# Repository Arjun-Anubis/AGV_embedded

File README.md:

# AGV Embedded Systems Selection Round

I attempted the first two tasks, the PCB design of the nPM1100 and the digital design of CORDIC in verilog

## Structure of the Repository

The task folders each have their directories, within the first level, the README.md
will have the info required to run the programs including installation directions etc
The documentation and approach will be in the doc folder

## Progress on the tasks

### PCB design

1. Base task (design req)
    a. Schematic
    b. Design 
    c. BOM
2. Expose CHG, ERR, ISET, MODE, SHPHLD and SHPACT pins to MCU
3. Status LEDs
4. Battery Monitoring

Constraints
1. Max Dimensions
2. SMD, top mounted
3. 0403-0805 footprints
4. Input via 2 pin header       NOTE
5. Max 4 copper layers
6. QFN24 footprint with used central thermal pad
7. 3V output
8. 200mA output

### Digital Design

1. Design
    a. n-bit adder
    b. complemts and subtracter
    c. comparator
    d. look up table
    e. 8 bit to 12 bit CORDIC
2. Test Bench
3. GTKWave

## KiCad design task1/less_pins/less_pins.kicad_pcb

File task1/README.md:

# PCB Design with the nPM1100 PMIC

This is documentaion written after the fact, if you want to read the 
design process as it was done, consider [the old readme](./README.old.md). 
I'll explain my model in two layers of abstraction.

1. Behaviour level
2. Pin level

## Behaviour level

A PMIC is typically used on a portable electronic device: like a mobile phone, 
a gaming mouse, a drone etc. it abstracts away the details of charging and battery
and provides a stable voltage and current to the microcontroller chip.

This means that our chip has the following

1. input (USB or barrel)
2. output (microcontroller)
3. inout (battery, which has to be charged and discharged)

and similarly out PMIC can itself be divided into subsystems

Now that we understand what the chip does on a high level, we need to check if this
is indeed the right chip for us to use, we can decide this by looking at the 
design requirements:

1. 3V DC output
2. 200mA charging
3. 35mmx35mm for the entire PCB

and we have been told to use the nordic semiconductor nPM1100 PMIC
with the QFN24 variant, which is 4mmx4mm.

First we make a ballpark estimate, then we consult the data sheet, the voltage ~ 3V
is pretty typical for a microcontroller so that makes sense, and the charging
current 200mA is pretty typical for a small LiPo battery, in say a drone.

The consumption current is probably less than that, and that would make the 
outut power a few hundred mW, which is also reasonable for a 35mmx35mm
chip to discharge

Now we consult the datasheet

### Package size

The 4mmx4mm package does indeed exist

> nPM1100 is an integrated Power Management IC (PMIC) with a linear-mode lithium-ion/lithium-polymer battery charger in a compact 2.1x2.1 mm WLCSP or 4.0x4.0 mm QFN package. It has a highly efficient DC/ DC buck regulator with configurable dual mode output.

and we can indeed order it, according to the datasheet, the exact variant we want is

> nPM1100-QDAA-XX

where the QD portion signifies the QFN package, and AA specifies the Vterm voltage

### Charging Current

We can indeed charge at 200mA 

> Configurable charge current with a resistor connected to the ICHG pin (from 20 mA to 400 mA)

and we need to use a 1.5k resistor according to the table

### Output voltage

We can indeed output a stable 3.0V using the buck regulator

> Configurable output voltage between 1.8 V and 3.0 

and we need to set both VOUTBSET pins high accourding to the table

## Pin Level

Now we have a high level overview of the scale and function of the chip, and we haev determined
that it can be appropriately used here, let us get into the nitty gritties. We need to make a few 
design choices

1. Which power input setting?

According to the datasheet, I can choose from four possible choices, of these I'm going to choose 
option 3, 

Why? Three reasons

a. We need atleast 200mA input for it to be able to charge the battery while also powering the device
and so I cant use the flat 100mA option
b. Flat 500mA is unsafe in the SDP case, in which case I risk bricking a laptop if I charge from that
essentially I wouldnt be following the USB spec
c. Exposing ISET requires (a) more pins to the MCU, and (b) also exposing the usb data line to the MCU
both of which, it may not have

2. Which battery parameters?
We need to set three parameters;

a. Ichg, which has to be 200mA and requires a 1.5k resistor (tolerance be damned :( )
b. Vtermset, which really depends on our battery, but I'll set it low, which is 4.1V cuz we're on standard
c. NTC, here I'll opt to just ignore this, because it seems that batteries with thermistors are rare
and it adds an extra pin, and we already need two pins for power and ground.

3. What sort of microcontoller header?

What do we absolutely need?
1. Vout
2. ground

What would be nice to have?
1. CHG
2. ERR

What would be _really_ nice to have?
1. Battery monitor with enable
2. Low battery indicator

What I'm not exposing?
1. MODE: why? the default is already automatic
2. ISET: I dont wanna expose the USB bus
3. SHPACT: too nihe a faeture to demand its own pin

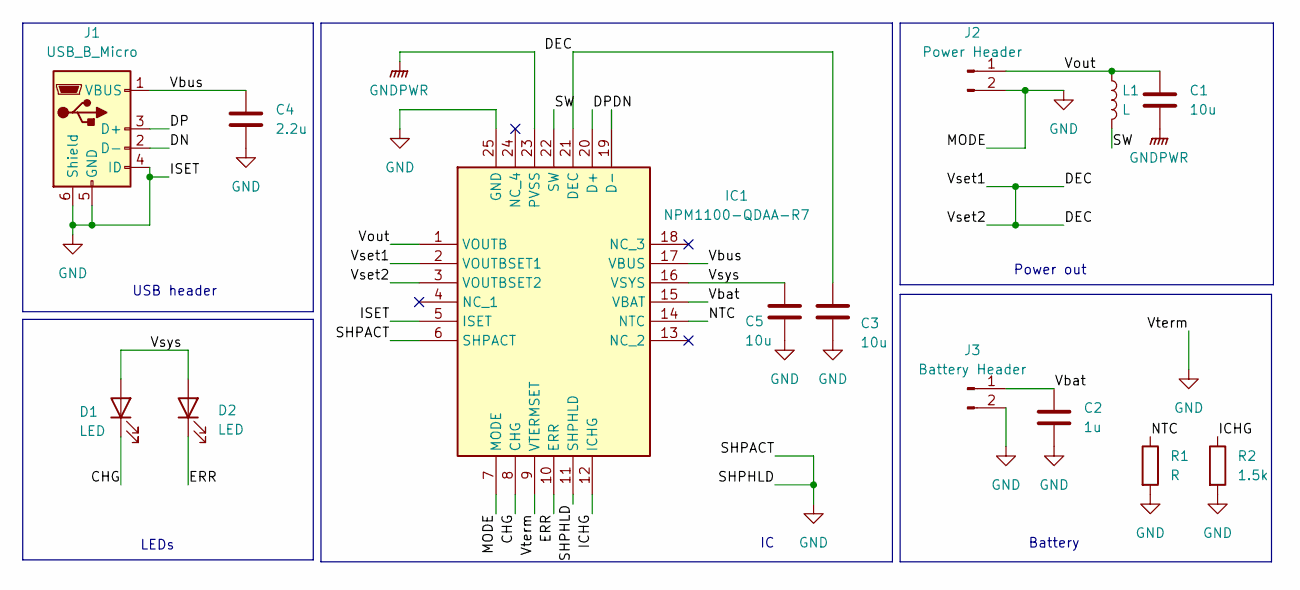
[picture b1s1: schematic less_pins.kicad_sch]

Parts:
C1, C3, C5: 10u; C_0603_1608Metric
C2: 1u; C_0603_1608Metric
C4: 2.2u; C_0603_1608Metric
D1, D2: LED; LED_0603_1608Metric
IC1: NPM1100-QDAA-R7; QFN50P400X400X90-25N-D; Mouser Part Number 949-NPM1100-QDAA-R7
J1: USB_B_Micro; USB_Micro-B_Amphenol_10104110_Horizontal
J2: Power Header; PinSocket_1x02_P2.54mm_Vertical
J3: Battery Header; JST_PH_B2B-PH-K_1x02_P2.00mm_Vertical
L1: L; L_0603_1608Metric
R1: R; R_0603_1608Metric
R2: 1.5k; R_0603_1608Metric

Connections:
/CHG: D1.1 (K), IC1.8 (CHG)
/DEC: C3.1, IC1.2 (VOUTBSET1), IC1.3 (VOUTBSET2), IC1.21 (DEC)
/DN: IC1.19 (D-), J1.2 (D-)
/DP: IC1.20 (D+), J1.3 (D+)
/ERR: D2.1 (K), IC1.10 (ERR)
/ICHG: IC1.12 (ICHG), R2.1
/NTC: IC1.14 (NTC), R1.1
/SW: IC1.22 (SW), L1.2
/Vbat: C2.1, IC1.15 (VBAT), J3.1
/Vbus: C4.1, IC1.17 (VBUS), J1.1 (VBUS)
/Vout: C1.1, IC1.1 (VOUTB), J2.1, L1.1
/Vsys: C5.2, D1.2 (A), D2.2 (A), IC1.16 (VSYS)
GND: C2.2, C3.2, C4.2, C5.1, IC1.5 (ISET), IC1.6 (SHPACT), IC1.7 (MODE), IC1.9 (VTERMSET), IC1.11 (SHPHLD), IC1.25 (GND), J1.4 (ID), J1.5 (GND), J1.6 (Shield), J2.2, J3.2, R1.2, R2.2
GNDPWR: C1.2, IC1.23 (PVSS)

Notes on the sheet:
LEDs
Battery
USB header
Power out

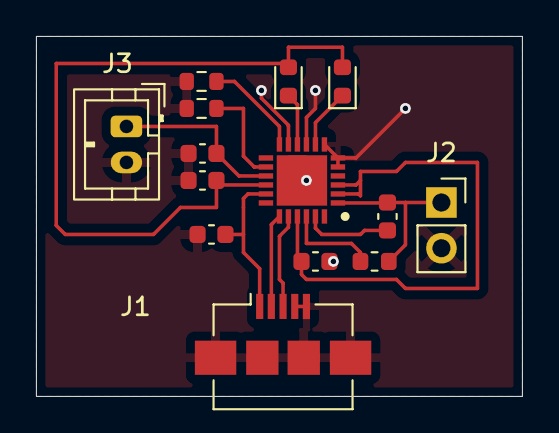
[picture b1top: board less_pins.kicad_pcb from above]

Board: 2 copper layers, 27.0 x 20.0 mm, 14 parts (0 on the bottom side), 14 nets.

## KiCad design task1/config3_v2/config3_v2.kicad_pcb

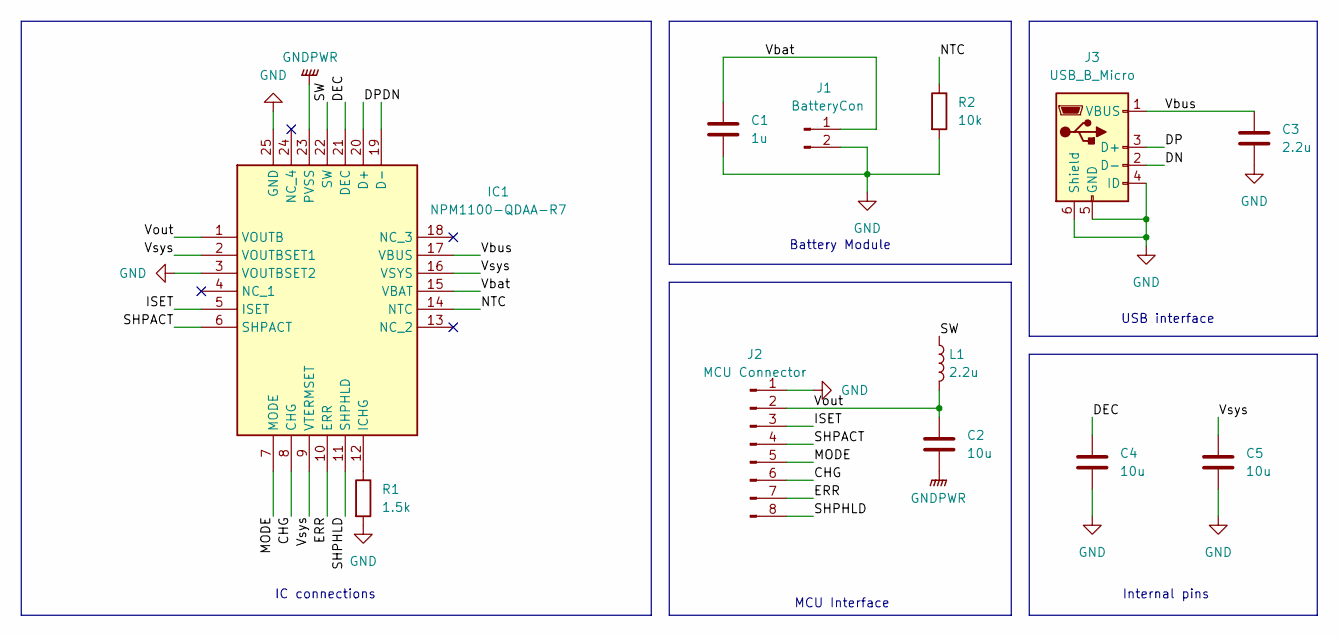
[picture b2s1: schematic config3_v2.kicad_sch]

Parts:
C1: 1u; C_0603_1608Metric
C2, C4, C5: 10u; C_0603_1608Metric
C3: 2.2u; C_0603_1608Metric
IC1: NPM1100-QDAA-R7; QFN50P400X400X90-25N-D; Mouser Part Number 949-NPM1100-QDAA-R7
J1: BatteryCon; JST_PH_B2B-PH-K_1x02_P2.00mm_Vertical
J2: MCU Connector; PinSocket_1x08_P2.54mm_Vertical
J3: USB_B_Micro; USB_Micro-B_Amphenol_10118194_Horizontal
L1: 2.2u; L_0805_2012Metric
R1: 1.5k; R_0603_1608Metric
R2: 10k; R_0603_1608Metric

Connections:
/CHG: IC1.8 (CHG), J2.6
/DEC: C4.1, IC1.21 (DEC)
/DN: IC1.19 (D-), J3.2 (D-)
/DP: IC1.20 (D+), J3.3 (D+)
/ERR: IC1.10 (ERR), J2.7
/ISET: IC1.5 (ISET), J2.3
/MODE: IC1.7 (MODE), J2.5
/NTC: IC1.14 (NTC), R2.1
/SHPACT: IC1.6 (SHPACT), J2.4
/SHPHLD: IC1.11 (SHPHLD), J2.8
/SW: IC1.22 (SW), L1.1
/Vbat: C1.1, IC1.15 (VBAT), J1.1
/Vbus: C3.1, IC1.17 (VBUS), J3.1 (VBUS)
/Vout: C2.1, IC1.1 (VOUTB), J2.2, L1.2
/Vsys: C5.1, IC1.2 (VOUTBSET1), IC1.9 (VTERMSET), IC1.16 (VSYS)
GND: C1.2, C3.2, C4.2, C5.2, IC1.3 (VOUTBSET2), IC1.25 (GND), J1.2, J2.1, J3.4 (ID), J3.5 (GND), J3.6 (Shield), R1.2, R2.2
GNDPWR: C2.2, IC1.23 (PVSS)
unnamed: IC1.12 (ICHG), R1.1

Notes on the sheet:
USB interface
Battery Module
MCU Interface
Internal pins
IC connections

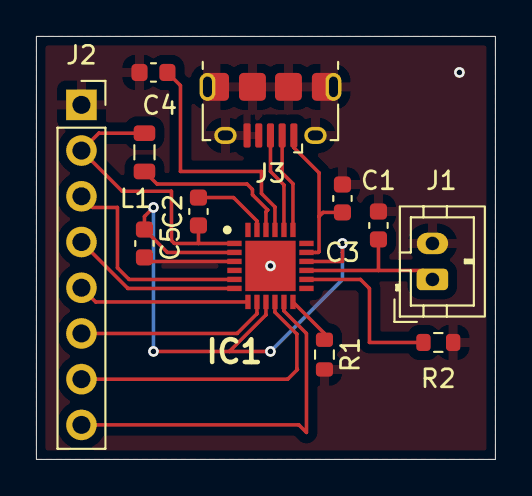
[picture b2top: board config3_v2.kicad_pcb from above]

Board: 2 copper layers, 25.5 x 23.5 mm, 12 parts (0 on the bottom side), 18 nets.

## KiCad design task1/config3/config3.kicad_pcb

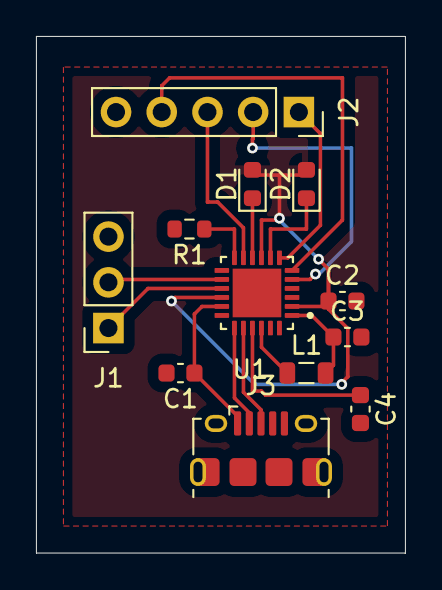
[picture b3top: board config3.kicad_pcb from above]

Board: 2 copper layers, 20.5 x 28.7 mm, 12 parts (0 on the bottom side), 17 nets.

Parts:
C1: 2.2u; C_0603_1608Metric
C2, C3, C4: 10u; C_0603_1608Metric
D1, D2: LED; LED_0603_1608Metric
J1: BatteryConnector; PinSocket_1x03_P2.54mm_Vertical
J2: OutputInterface; PinSocket_1x05_P2.54mm_Vertical
J3: USB_B_Micro; USB_Micro-B_Amphenol_10118194_Horizontal
L1: L; L_0805_2012Metric
R1: 1.5k; R_0603_1608Metric
U1: NPM1100-QDAB-R7; QFN50P400X400X90-25N

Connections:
/DEC: C4.1, U1.21 (DEC)
/DN: J3.2 (D-), U1.19 (D-)
/DP: J3.3 (D+), U1.20 (D+)
/ISET: J2.2, U1.5 (ISET)
/MODE: J2.1, U1.7 (MODE)
/NTC: J1.2, U1.14 (NTC)
/SHPACT: J2.4, U1.6 (SHPACT)
/SHPHLD: J2.3, U1.11 (SHPHLD)
/Vbat: J1.1, U1.15 (VBAT)
/Vbus: C1.1, J3.1 (VBUS), U1.17 (VBUS)
/Vout: C3.1, L1.2, U1.1 (VOUTB)
/Vsys: C2.1, D1.2 (A), D2.2 (A), U1.2 (VOUTBSET1), U1.9 (VTERMSET), U1.16 (VSYS)
GND: C1.2, C2.2, C3.2, C4.2, J1.3, J2.5, J3.5 (GND), J3.6 (Shield), R1.2, U1.3 (VOUTBSET2), U1.23 (PVSS), U1.25 (EXP)
unnamed: D1.1 (K), U1.10 (ERR)
unnamed: D2.1 (K), U1.8 (CHG)
unnamed: R1.1, U1.12 (ICHG)
unnamed: L1.1, U1.22 (SW)

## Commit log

2026-03-10 Added the initial research work on task1
2026-03-10 fixed link
2026-03-10 moved the screenshot and added it to the README
2026-03-10 removed the block diagram ss
2026-03-10 Added referece circuit config 1
2026-03-25 Added verilog task
2026-03-25 Re did README
2026-03-25 Improved README
2026-03-25 fixed pictures
2026-03-25 Added design decisions
2026-03-25 Added the whole project
2026-03-25 Added the math behind cordic
2026-03-25 Finished the add free cordic, cleaned up
2026-03-27 added a new build
2026-03-27 fixed up the readme in task2
